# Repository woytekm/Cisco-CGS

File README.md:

# Cisco-CGS
Recreating parts for Cisco CGS router

This project is related to a restoration of one of the first Cisco products: CGS Router

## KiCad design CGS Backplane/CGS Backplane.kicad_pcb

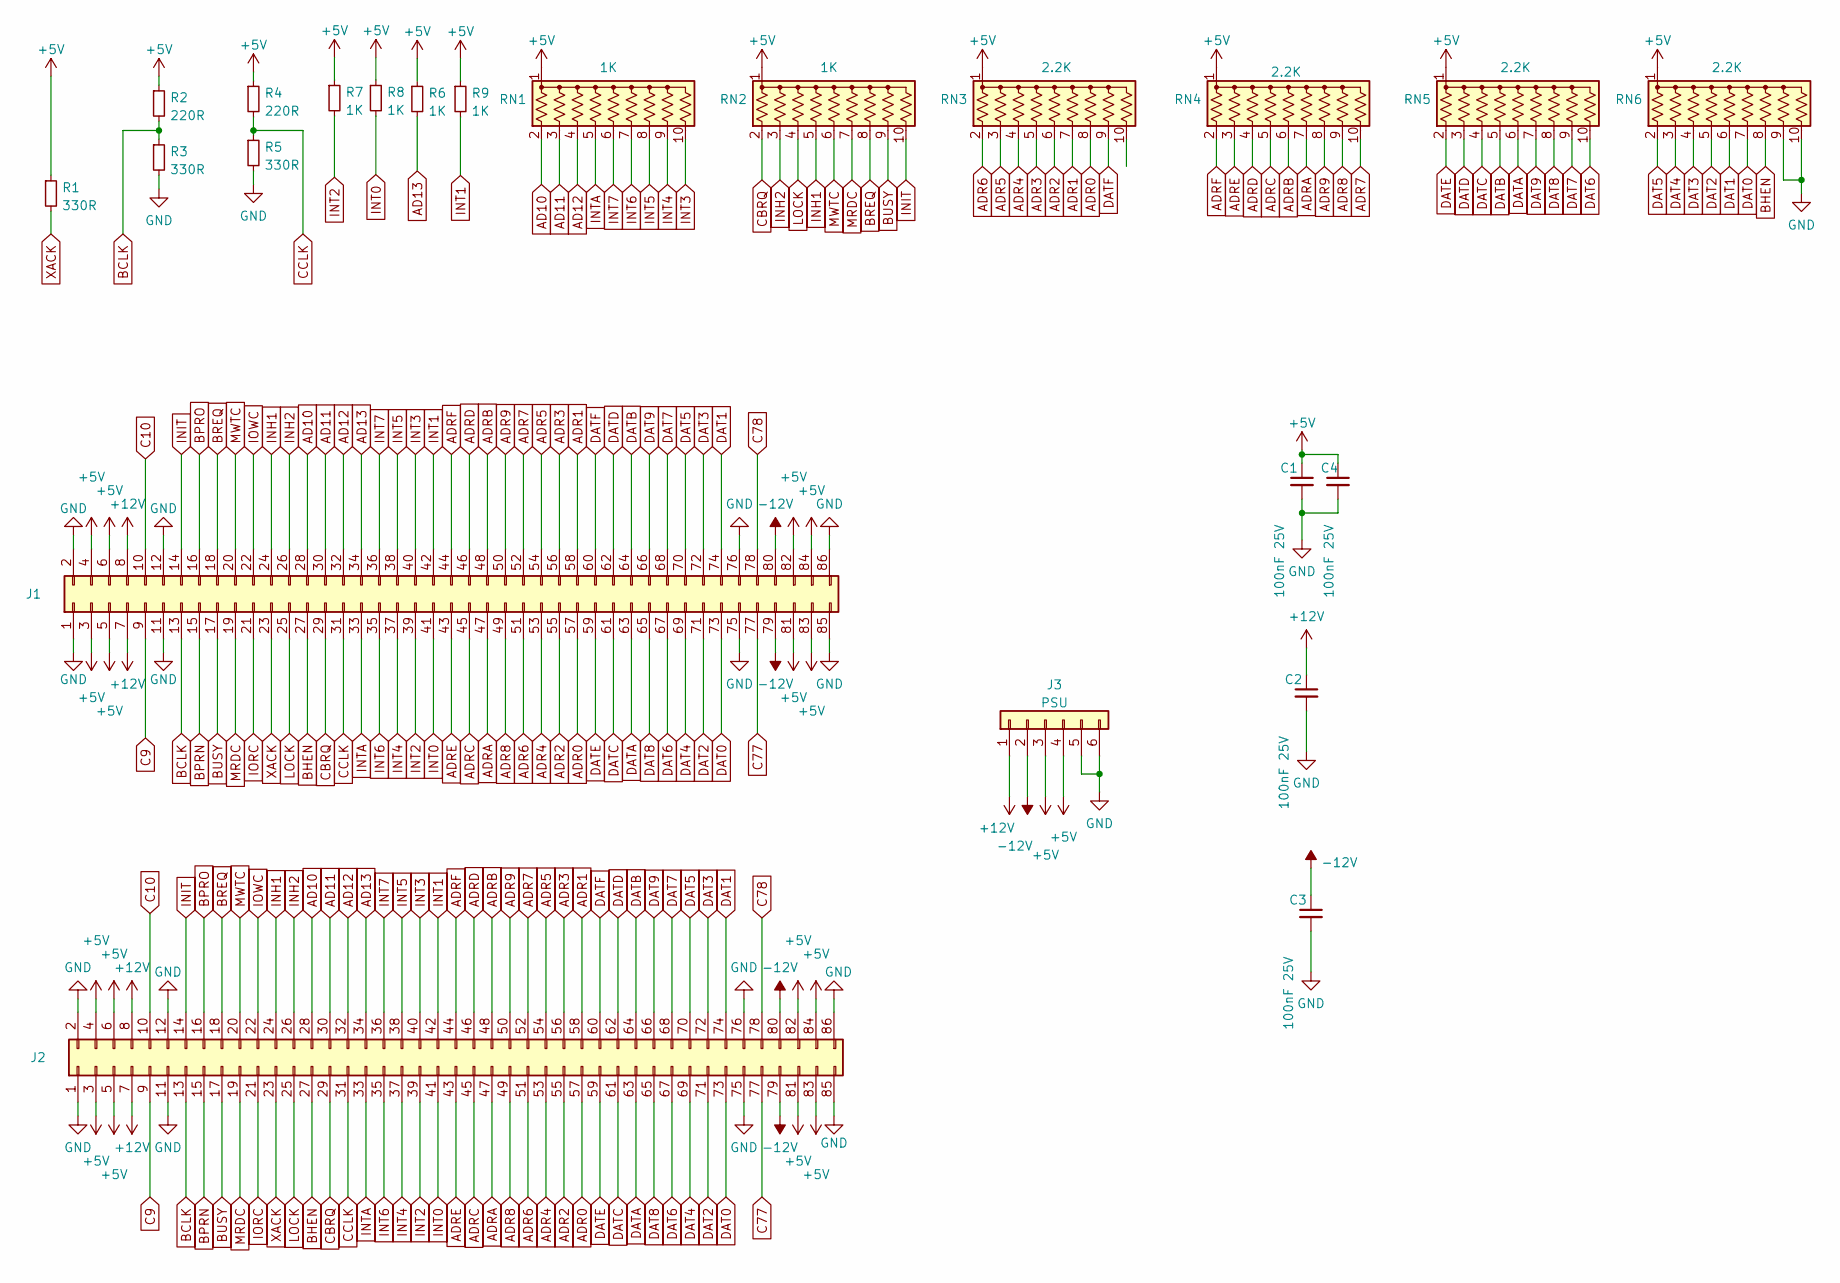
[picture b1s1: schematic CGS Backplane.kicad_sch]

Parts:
C1, C2, C3, C4: 100nF 25V; C_Rect_L7.0mm_W2.0mm_P5.00mm
J1, J2: Conn_02x43_Odd_Even; Conn_2x43_3.96mm
J3: PSU; Wago_734-136_1x06_P3.50mm_Vertical
R1, R3, R5: 330R; R_Axial_DIN0204_L3.6mm_D1.6mm_P5.08mm_Horizontal
R2, R4: 220R; R_Axial_DIN0204_L3.6mm_D1.6mm_P5.08mm_Horizontal
R6, R7, R8, R9: 1K; R_Axial_DIN0204_L3.6mm_D1.6mm_P5.08mm_Horizontal
RN1, RN2: 1K; R_Array_SIP10
RN3, RN4, RN5, RN6: 2.2K; R_Array_SIP10

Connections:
+5V: C1.1, C4.1, J1.3, J1.4, J1.5, J1.6, J1.81, J1.82, J1.83, J1.84, J2.3, J2.4, J2.5, J2.6, J2.81, J2.82, J2.83, J2.84, J3.3, J3.4, R1.1, R2.1, R4.1, R6.1, R7.1, R8.1, R9.1, RN1.1 (common), RN2.1 (common), RN3.1 (common), RN4.1 (common), RN5.1 (common), RN6.1 (common)
+12V: C2.1, J1.7, J1.8, J2.7, J2.8, J3.1
-12V: C3.1, J1.79, J1.80, J2.79, J2.80, J3.2
AD10: J1.28, J2.28, RN1.2 (R1)
AD11: J1.30, J2.30, RN1.3 (R2)
AD12: J1.32, J2.32, RN1.4 (R3)
AD13: J1.34, J2.34, R6.2
ADR0: J1.57, J2.57, RN3.8 (R7)
ADR1: J1.58, J2.58, RN3.7 (R6)
ADR2: J1.55, J2.55, RN3.6 (R5)
ADR3: J1.56, J2.56, RN3.5 (R4)
ADR4: J1.53, J2.53, RN3.4 (R3)
ADR5: J1.54, J2.54, RN3.3 (R2)
ADR6: J1.51, J2.51, RN3.2 (R1)
ADR7: J1.52, J2.52, RN4.10 (R9)
ADR8: J1.49, J2.49, RN4.9 (R8)
ADR9: J1.50, J2.50, RN4.8 (R7)
ADRA: J1.47, J2.47, RN4.7 (R6)
ADRB: J1.48, J2.48, RN4.6 (R5)
ADRC: J1.45, J2.45, RN4.5 (R4)
ADRD: J1.46, J2.46, RN4.4 (R3)
ADRE: J1.43, J2.43, RN4.3 (R2)
ADRF: J1.44, J2.44, RN4.2 (R1)
BCLK: J1.13, J2.13, R2.2, R3.1
BHEN: J1.27, J2.27, RN6.8 (R7)
BPRN: J1.15, J2.15
BPRO: J1.16, J2.16
BREQ: J1.18, J2.18, RN2.8 (R7)
BUSY: J1.17, J2.17, RN2.9 (R8)
C9: J1.9, J2.9
C10: J1.10, J2.10
C77: J1.77, J2.77
C78: J1.78, J2.78
CBRQ: J1.29, J2.29, RN2.2 (R1)
CCLK: J1.31, J2.31, R4.2, R5.1
DAT0: J1.73, J2.73, RN6.7 (R6)
DAT1: J1.74, J2.74, RN6.6 (R5)
DAT2: J1.71, J2.71, RN6.5 (R4)
DAT3: J1.72, J2.72, RN6.4 (R3)
DAT4: J1.69, J2.69, RN6.3 (R2)
DAT5: J1.70, J2.70, RN6.2 (R1)
DAT6: J1.67, J2.67, RN5.10 (R9)
DAT7: J1.68, J2.68, RN5.9 (R8)
DAT8: J1.65, J2.65, RN5.8 (R7)
DAT9: J1.66, J2.66, RN5.7 (R6)
DATA: J1.63, J2.63, RN5.6 (R5)
DATB: J1.64, J2.64, RN5.5 (R4)
DATC: J1.61, J2.61, RN5.4 (R3)
DATD: J1.62, J2.62, RN5.3 (R2)
DATE: J1.59, J2.59, RN5.2 (R1)
DATF: J1.60, J2.60, RN3.9 (R8)
INH1: J1.24, J2.24, RN2.5 (R4)
INH2: J1.26, J2.26, RN2.3 (R2)
INIT: J1.14, J2.14, RN2.10 (R9)
INT0: J1.41, J2.41, R8.2
INT1: J1.42, J2.42, R9.2
INT2: J1.39, J2.39, R7.2
INT3: J1.40, J2.40, RN1.10 (R9)
INT4: J1.37, J2.37, RN1.9 (R8)
INT5: J1.38, J2.38, RN1.8 (R7)
INT6: J1.35, J2.35, RN1.7 (R6)
INT7: J1.36, J2.36, RN1.6 (R5)
INTA: J1.33, J2.33, RN1.5 (R4)
IORC: J1.21, J2.21
IOWC: J1.22, J2.22
LOCK: J1.25, J2.25, RN2.4 (R3)
MRDC: J1.19, J2.19, RN2.7 (R6)
MWTC: J1.20, J2.20, RN2.6 (R5)
XACK: J1.23, J2.23, R1.2

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
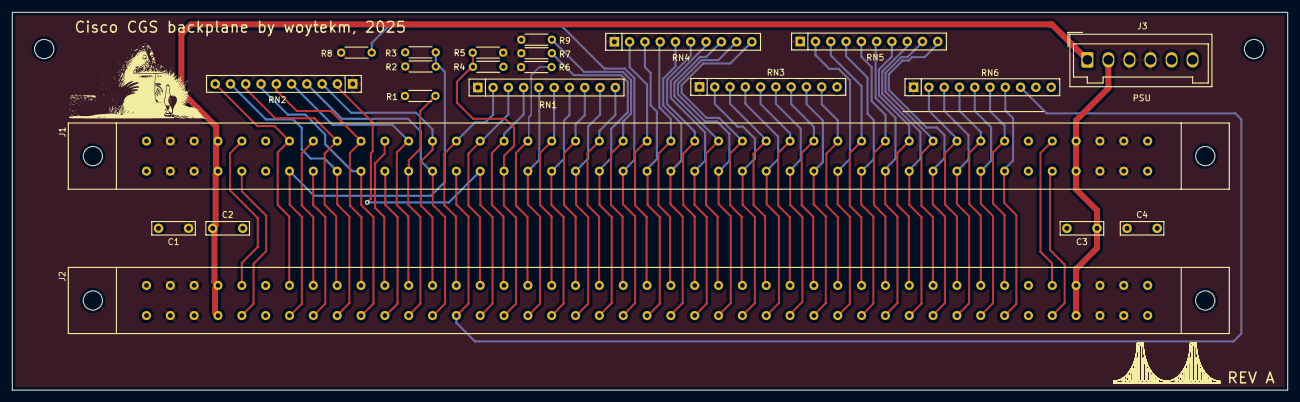
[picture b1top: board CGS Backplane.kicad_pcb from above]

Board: 2 copper layers, 212.0 x 62.8 mm, 22 parts (0 on the bottom side), 70 nets.

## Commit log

2026-01-24 move files
2026-01-24 move files to proper place
